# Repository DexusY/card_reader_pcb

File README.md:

# ESP32 RFID Access Control System

A compact and robust access control system based on the **ESP32-WROOM-32E** microcontroller and the **RFID-RC522** reader. This project allows for controlling an electric strike, electromagnetic lock, or gate upon presenting an authorized card.

The system is designed to run on **12V DC**, making it easy to integrate with standard alarm and intercom systems.

---

## PCB Visualization

The PCB design (2-layer) prioritizes power stability and RF signal integrity.

### Key PCB Features:
* **RF Optimization:** Dedicated "Keep-out zone" under the ESP32 antenna to ensure maximum WiFi/Bluetooth range.
* **Stable Power Delivery:** Wide power rails for the 3.3V line to prevent voltage drops during high current peaks.
* **Safety:** Physical isolation slots routed near the relay to increase creepage distance and safety.

---

## Schematic & Functional Description

The system is divided into three main functional blocks.

### 1. Power Supply Section
The input stage accepts **12V DC**. It utilizes a modern **LMR51610** (SOT-23-6) step-down converter to efficiently lower the voltage to the **3.3V** required by the ESP32 and RFID module.
* **Input:** 12V DC (Screw Terminal J1).
* **Filtering:** Ceramic capacitors and a 1.5uH inductor ensure a stable output.

### 2. MCU & User Interface
The core of the system is the **ESP32-WROOM-32E**. It handles the logic, wireless communication, and user feedback:
* **Feedback:** A Buzzer (BZ1) and 3 LEDs (Red, Yellow, Green) indicate access status.
* **Programming:** Exposed UART header (J3) with TX, RX, GND, 3.3V, IO0 (BOOT), and EN pins.

### 3. Actuator Output
The lock control mechanism is driven by a relay via an NPN transistor (Q1).
* **Output:** Screw Terminal J4 (NO - Normally Open contact).
* **Protection:** A flyback diode (D5) protects the transistor from voltage spikes generated by the relay coil.

---

##  Pinout & Connectors

| Designator | Type | Description |
| :--- | :--- | :--- |
| **J1** | Screw Terminal | **12V DC** Power Input |
| **J2** | Pin Header 1x8 | **RFID-RC522** Module Connector (SPI) |
| **J3** | Pin Header 1x5 | UART Programming Port (TX, RX, RST, BOOT, GND) |
| **J4** | Screw Terminal | Relay Output (Connect to Electric Strike) |

---

##  Bill of Materials (Key Components)

* **MCU:** ESP32-WROOM-32E (WiFi/BT Module)
* **Regulator:** LMR51610XF (DC-DC Step-Down)
* **Relay:** 12V Coil (Miniature SPST/SPDT)
* **Transistor:** NPN (e.g., BC817, SOT-23)
* **Inductor:** 1.5uH (Power inductor for the buck converter)
* **RFID:** RC522 Reader Module (connects to J2)

---

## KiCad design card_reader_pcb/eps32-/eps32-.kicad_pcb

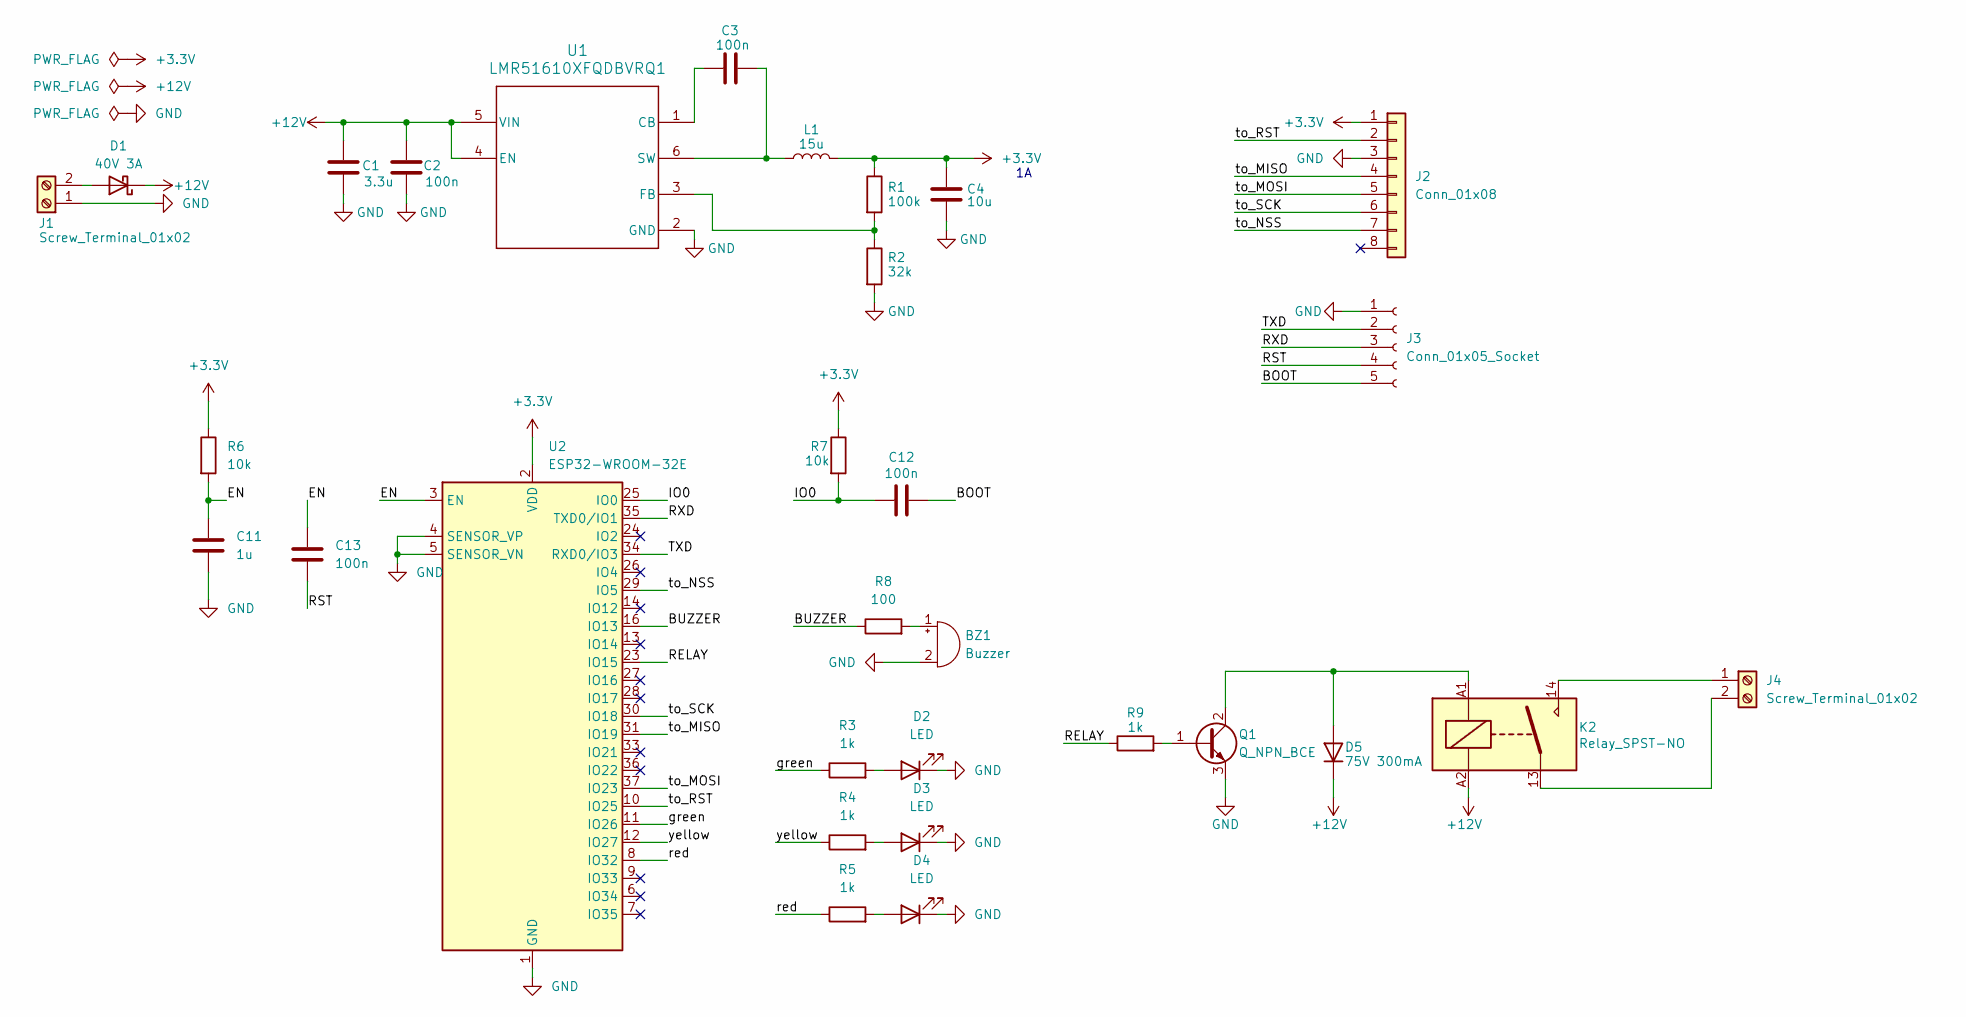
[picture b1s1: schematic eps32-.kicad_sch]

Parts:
BZ1: Buzzer; Buzzer_TDK_PS1240P02BT_D12.2mm_H6.5mm
C1: 3.3u; C_0201_0603Metric
C2, C3, C12, C13: 100n; C_0201_0603Metric
C4: 10u; C_0201_0603Metric
C11: 1u; C_0201_0603Metric
D1: 40V 3A; D_0402_1005Metric
D2, D3, D4: LED; LED_0201_0603Metric
D5: 75V 300mA; D_0201_0603Metric
J1, J4: Screw_Terminal_01x02; TerminalBlock_MaiXu_MX126-5.0-02P_1x02_P5.00mm
J2: Conn_01x08; PinSocket_1x08_P1.00mm_Vertical
J3: Conn_01x05_Socket; PinHeader_1x05_P1.00mm_Vertical
K2: Relay_SPST-NO; Relay_SPST_Finder_32.21-x300
L1: 15u; L_6.3x6.3_H3
Q1: Q_NPN_BCE; SOT-23
R1: 100k; R_0603_1608Metric
R2: 32k; R_0603_1608Metric
R3, R4, R5, R9: 1k; R_0603_1608Metric
R6, R7: 10k; R_0603_1608Metric
R8: 100; R_0603_1608Metric
U1: LMR51610XFQDBVRQ1; DBV0006A-IPC_C
U2: ESP32-WROOM-32E

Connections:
+3.3V: C4.1, J2.1, L1.2, R1.1, R6.1, R7.1, U2.2 (VDD)
+12V: C1.1, C2.1, D1.1 (K), D5.1 (K), K2.A2, U1.4 (EN), U1.5 (VIN)
/BOOT: C12.2, J3.5
/BUZZER: R8.1, U2.16 (IO13)
/EN: C11.1, C13.1, R6.2, U2.3 (EN)
/IO0: C12.1, R7.2, U2.25 (IO0)
/RELAY: R9.1, U2.23 (IO15)
/RST: C13.2, J3.4
/RXD: J3.3, U2.35 (TXD0/IO1)
/TXD: J3.2, U2.34 (RXD0/IO3)
/green: R3.1, U2.11 (IO26)
/red: R5.1, U2.8 (IO32)
/to_MISO: J2.4, U2.31 (IO19)
/to_MOSI: J2.5, U2.37 (IO23)
/to_NSS: J2.7, U2.29 (IO5)
/to_RST: J2.2, U2.10 (IO25)
/to_SCK: J2.6, U2.30 (IO18)
/yellow: R4.1, U2.12 (IO27)
GND: BZ1.2 (-), C1.2, C2.2, C4.2, C11.2, D2.1 (K), D3.1 (K), D4.1 (K), J1.1, J2.3, J3.1, Q1.3 (E), R2.2, U1.2 (GND), U2.1 (GND), U2.4 (SENSOR_VP), U2.5 (SENSOR_VN), U2.15 (GND), U2.38 (GND), U2.39 (GND)
unnamed: BZ1.1 (+), R8.2
unnamed: D1.2 (A), J1.2
unnamed: D2.2 (A), R3.2
unnamed: D3.2 (A), R4.2
unnamed: D4.2 (A), R5.2
unnamed: D5.2 (A), K2.A1, Q1.2 (C)
unnamed: J4.1, K2.14
unnamed: J4.2, K2.13
unnamed: Q1.1 (B), R9.2
unnamed: C3.1, U1.1 (CB)
unnamed: R1.2, R2.1, U1.3 (FB)
unnamed: C3.2, L1.1, U1.6 (SW)

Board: 2 copper layers, 31 parts (0 on the bottom side), 31 nets, no tracks yet.

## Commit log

2025-10-19 Add initial content to README.md
2025-11-04 Enhance README with project details and components
    Added detailed project description and component list for ESP32 development board.
2025-11-11 Revise project features and components in README
    Changed project components, added small features
2025-11-11 Update README to correct NFC to RFID terminology
2025-12-03 Revise README for ESP32 RFID Access Control System
    Updated project description and added key features of the ESP32 RFID Access Control System. Enhanced PCB visualization and functional description sections.
